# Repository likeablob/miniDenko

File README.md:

# miniDenko - A portable messaging device
`miniDenko` (Denko = 電光 is from "an electric scoreboard" in Japanese) is a portable messaging device.

Or LED Matrix + ESP8266 + MPU6050 + Modern Web framework(Vue.js + Buefy) = A hackable LED messaging platform

## Features
- Edit & save your message and show it up instantly.(Sub-second booting)
  - Also supports Japanese characters thanks to [Arduino-misakiUTF16](https://github.com/Tamakichi/Arduino-misakiUTF16) lib written by [[Tamakichi]](https://github.com/Tamakichi) san.
- Easily connectable with Phones, Laptops, etc. via WiFi.
  - Supports `STA`, `AP`, `AP_STA` modes to collaborate with the devices.
- Made from easily-obtainable parts. (See [#BOM](#BOM))
- Its [portable and slim shape](./openscad/minidenko-case-body-opaque.stl) fits in your (large) pocket.

- And as a latest gadget should be, equipped with the **Type-C** charging port.

## Project structure
- [`pio/`](./pio) - code for the firmware(PlatformIO)
- [`pio/webui/`](./pio/webui) - code for the WebUI(Vue.js + Buefy)
- [`kicad/`](./kicad) - PCB design (KiCad)
- [`gerber/`](./gerber) - PCB gerber files (KiCad)
- [`openscad/`](./openscad) - models for the 3D-printable case. (OpenSCAD)

## Gallery
|                                                                                                                                                                   | Descriptions              |
| ----------------------------------------------------------------------------------------------------------------------------------------------------------------- | ------------------------- |
|                                                                                 | Front view                |
|                                                                             | Side view (Charging port) |
|                                                                               | Side view (Power SW)      |
|                                                                                   | PCB                       |
|   | Web UI                    |

## BOM
| Name                                    | Quantity | Descriptions |
| --------------------------------------- | :------: | ------------ |
| ESP-12F (ESP8266 module)                |    1     |              |
| 32x8 LED matrix module (MAX7219)        |    1     |              |
| GY-521 (MPU6050 module)                 |    1     | 8 pins       |
| 350mAh LiPo battery                     |    1     | 19x36x8.5 mm |
| Type-C LiPo charging board (TP4056)     |    1     | 28x17.3 mm   |
| 10k ohm resistor (0805_2012Metric)      |    4     |              |
| 33k ohm resistor (0805_2012Metric)      |    1     |              |
| 1uF ceramic capacitor (0805_2012Metric) |    1     |              |
| 3.3V LDO xc6206p332mr (SOT-23)          |    1     |              |
| SPDT rocker switch (10x15 mm)           |    1     |              |
| M1.2 x 5 mm self tapping screw          |    4     |              |
| M2 x 6 mm self tapping screw            |    2     |              |

## Build instructions
https://hackaday.io/project/167747/instructions

## Refs
- https://www.thingiverse.com/thing:3876563
- https://hackaday.io/project/167747-minidenko
  
## License
MIT

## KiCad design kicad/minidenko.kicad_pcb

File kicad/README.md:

# miniDenko/PCB

## Prerequisites
- Install [KiCAD](https://platformio.org/) v5.0.1

## Credits
- [ESP-12E.kicad_mod](./lib_ext/ESP-12E.kicad_mod): borrowed from [jdunmire/kicad-ESP8266](https://github.com/jdunmire/kicad-ESP8266/tree/70e6530de5e3cae4ae77a4bca7d73b20a0af6baf)
- [MSK12C02.kicad_mod](./lib_ext/MSK12C02.kicad_mod): borrowed from [ElectronicCats/ElectronicCats-KiCad-Libraries](https://github.com/ElectronicCats/ElectronicCats-KiCad-Libraries/tree/df452181bf0b37c41caa9d8791b5432d5b44f4c0)

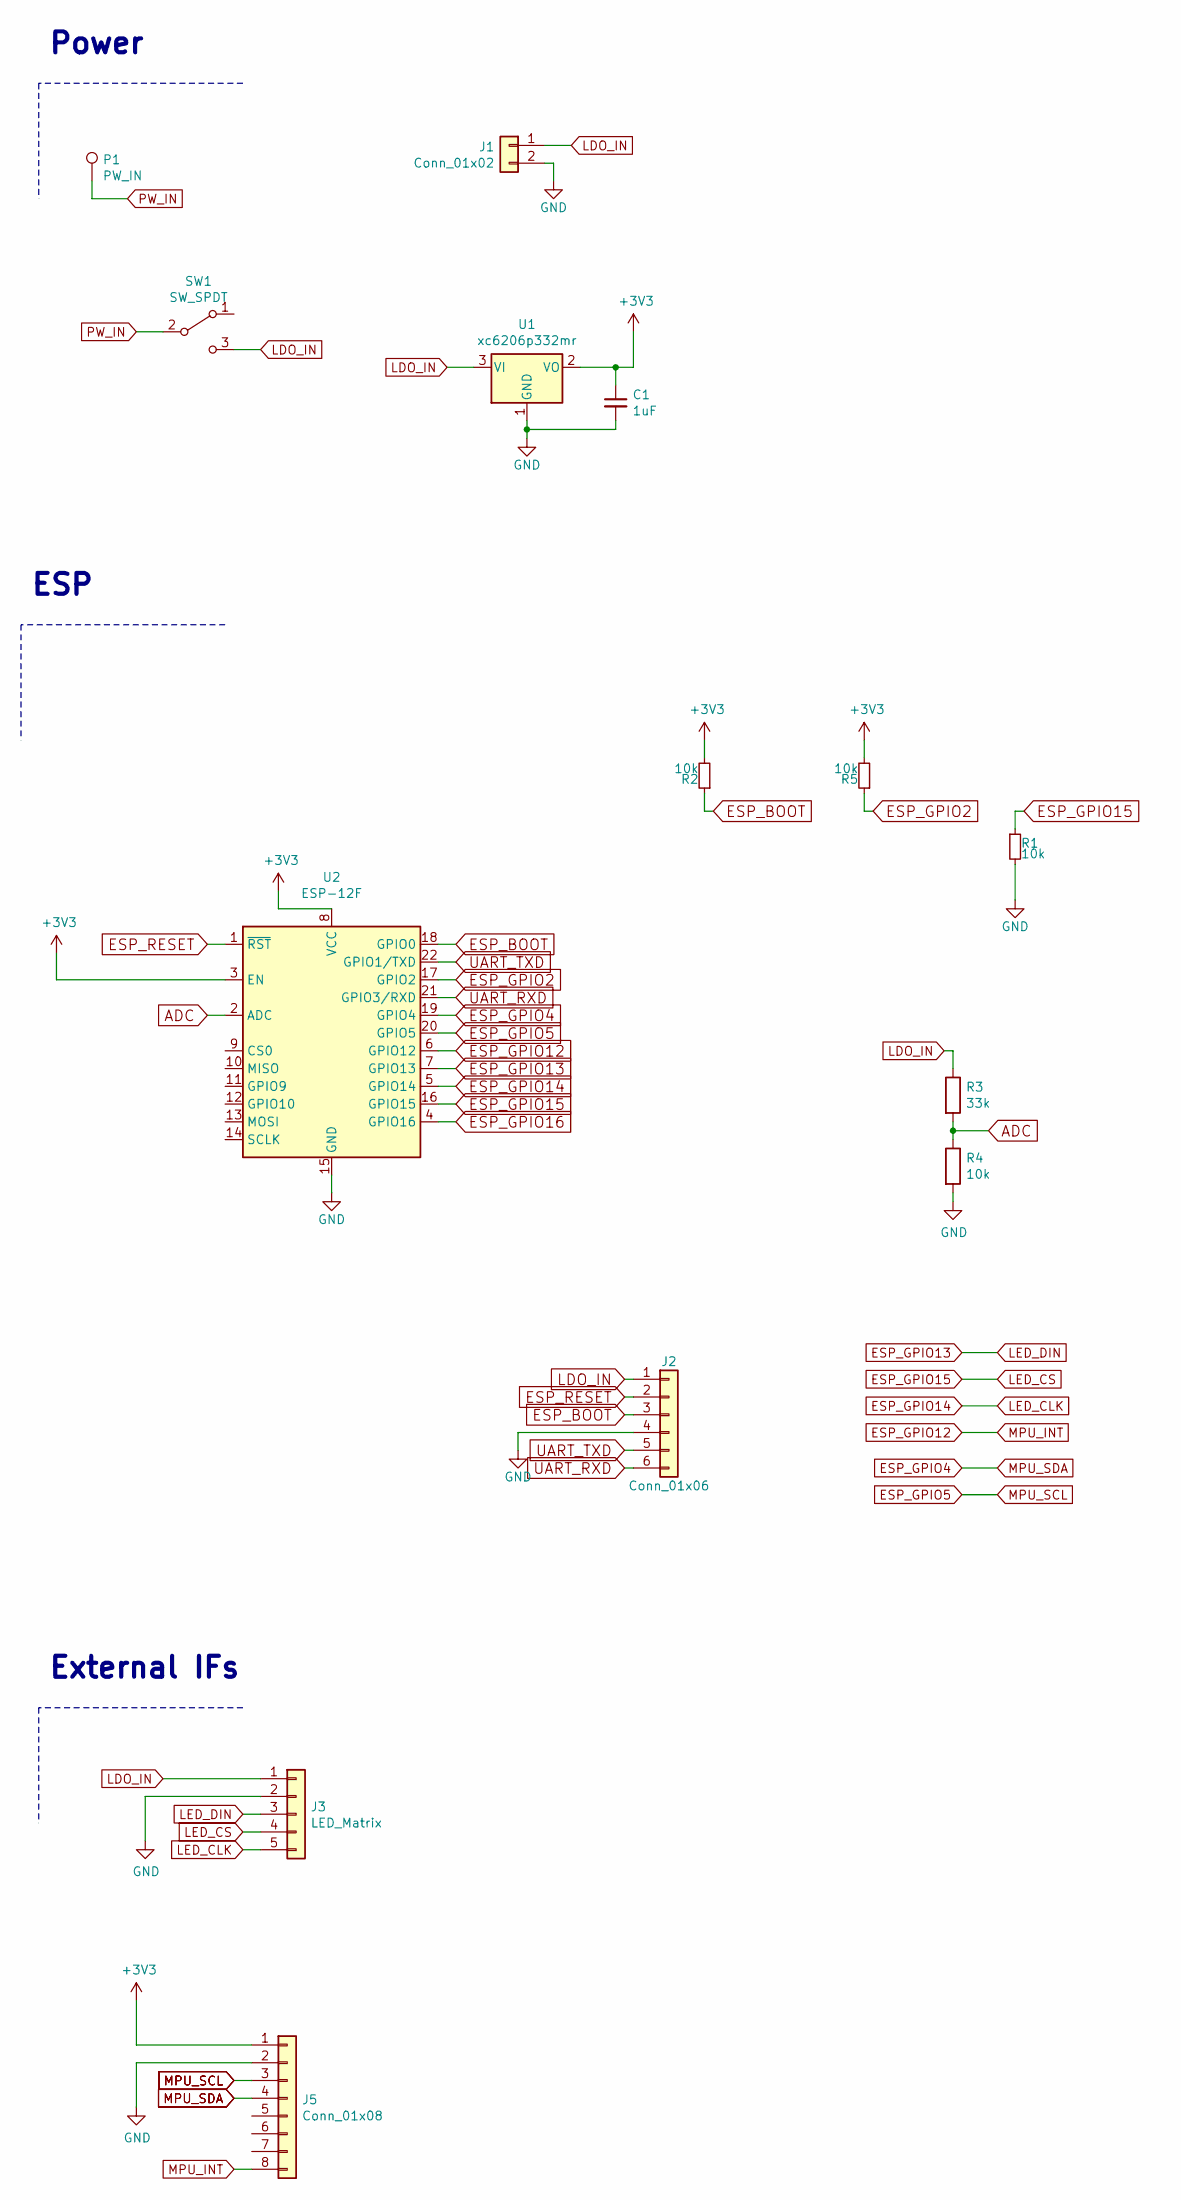
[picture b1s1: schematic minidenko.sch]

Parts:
C1: 1uF; C_0805_2012Metric_Pad1.15x1.40mm_HandSolder
J1: Conn_01x02; PinHeader_1x02_P2.54mm_Vertical
J2: Conn_01x06; PinHeader_1x06_P2.54mm_Vertical
J3: LED_Matrix; LED_Matrix_1x05_P2.54mm
J5: Conn_01x08; PinHeader_1x08_P2.54mm_Vertical
P1: PW_IN; TestPoint_Pad_1.5x1.5mm
R1, R2, R4, R5: 10k; R_0805_2012Metric
R3: 33k; R_0805_2012Metric
SW1: SW_SPDT; MSK12C02
U1: xc6206p332mr; SOT-23_Handsoldering
U2: ESP-12F; ESP-12E

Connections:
+3V3: C1.1, J5.1, R2.2, R5.2, U1.2 (VO), U2.3 (EN), U2.8 (VCC)
ADC: R3.2, R4.1, U2.2 (ADC)
ESP_BOOT: J2.3, R2.1, U2.18 (GPIO0)
ESP_GPIO2: R5.1, U2.17 (GPIO2)
ESP_GPIO4: J5.4, U2.19 (GPIO4)
ESP_GPIO5: J5.3, U2.20 (GPIO5)
ESP_GPIO12: J5.8, U2.6 (GPIO12)
ESP_GPIO13: J3.3, U2.7 (GPIO13)
ESP_GPIO14: J3.5, U2.5 (GPIO14)
ESP_GPIO15: J3.4, R1.1, U2.16 (GPIO15)
ESP_GPIO16: U2.4 (GPIO16)
ESP_RESET: J2.2, U2.1 (~RST)
GND: C1.2, J1.2, J2.4, J3.2, J5.2, R1.2, R4.2, U1.1 (GND), U2.15 (GND)
LDO_IN: J1.1, J2.1, J3.1, R3.1, SW1.3 (C), U1.3 (VI)
PW_IN: P1.1, SW1.2 (B)
UART_RXD: J2.6, U2.21 (GPIO3/RXD)
UART_TXD: J2.5, U2.22 (GPIO1/TXD)

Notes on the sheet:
ESP
Power
External IFs

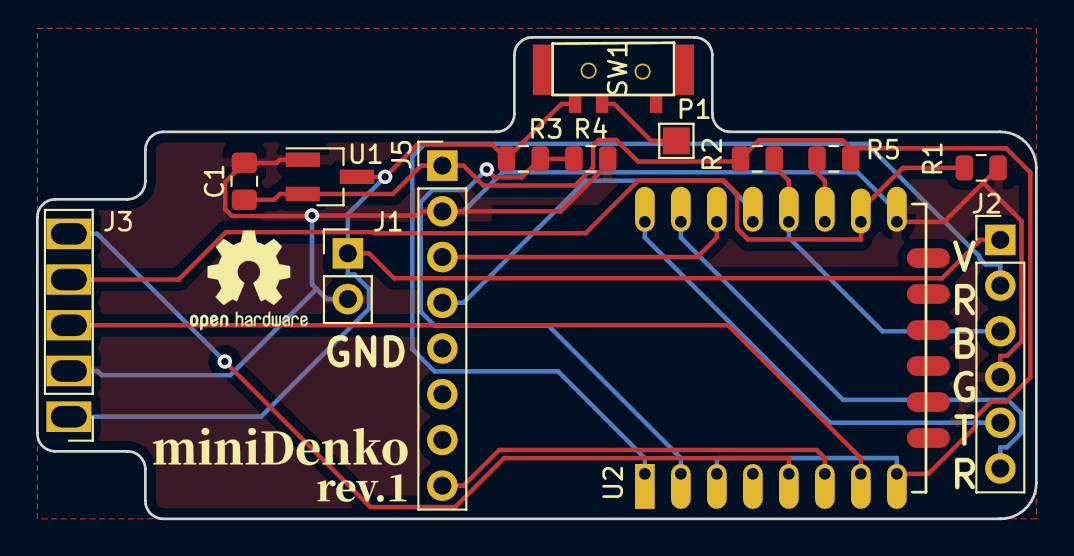
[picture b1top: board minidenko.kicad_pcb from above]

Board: 2 copper layers, 55.5 x 26.8 mm, 17 parts (1 on the bottom side), 16 nets.

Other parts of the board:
G1: LOGO; logo-minidenko-rev1
G2: OSHW-Logo2_7.3x6mm_SilkScreen
G3: LOGO; gomi_8x8

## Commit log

2019-09-24 Add files
2019-09-25 Add rev2 logo
2019-09-26 modify README.md format
2019-09-26 Add PCB files
2019-09-26 Upgrade dependencies
2019-09-26 Modify README.md - Add BOM - Minor tweak
2019-09-26 Modify README.md - Add Gellery section - Minor tweaks
2019-09-26 Modify openscad/README - Add print settings
2019-09-27 Fix validation for a void message
2019-09-29 Modify READMEs - Minor tweaks - Add pindef for the ISP port
2019-09-29 Add json-server/db.json
2020-06-07 Bump websocket-extensions from 0.1.3 to 0.1.4 in /pio/webui
    Bumps [websocket-extensions](https://github.com/faye/websocket-extensions-node) from 0.1.3 to 0.1.4.
    - [Release notes](https://github.com/faye/websocket-extensions-node/releases)
    - [Changelog](https://github.com/faye/websocket-extensions-node/blob/master/CHANGELOG.md)
    - [Commits](https://github.com/faye/websocket-extensions-node/compare/0.1.3...0.1.4)
2020-07-18 Bump lodash from 4.17.15 to 4.17.19 in /pio/webui
    Bumps [lodash](https://github.com/lodash/lodash) from 4.17.15 to 4.17.19.
    - [Release notes](https://github.com/lodash/lodash/releases)
    - [Commits](https://github.com/lodash/lodash/compare/4.17.15...4.17.19)
2020-07-31 Bump elliptic from 6.5.1 to 6.5.3 in /pio/webui
    Bumps [elliptic](https://github.com/indutny/elliptic) from 6.5.1 to 6.5.3.
    - [Release notes](https://github.com/indutny/elliptic/releases)
    - [Commits](https://github.com/indutny/elliptic/compare/v6.5.1...v6.5.3)
2020-09-04 Bump node-sass from 4.12.0 to 4.13.1 in /pio/webui
    Bumps [node-sass](https://github.com/sass/node-sass) from 4.12.0 to 4.13.1.
    - [Release notes](https://github.com/sass/node-sass/releases)
    - [Changelog](https://github.com/sass/node-sass/blob/master/CHANGELOG.md)
    - [Commits](https://github.com/sass/node-sass/compare/v4.12.0...v4.13.1)
2020-09-10 Bump http-proxy from 1.18.0 to 1.18.1 in /pio/webui
    Bumps [http-proxy](https://github.com/http-party/node-http-proxy) from 1.18.0 to 1.18.1.
    - [Release notes](https://github.com/http-party/node-http-proxy/releases)
    - [Changelog](https://github.com/http-party/node-http-proxy/blob/master/CHANGELOG.md)
    - [Commits](https://github.com/http-party/node-http-proxy/compare/1.18.0...1.18.1)
2020-11-25 Bump highlight.js from 9.15.10 to 9.18.5 in /pio/webui
    Bumps [highlight.js](https://github.com/highlightjs/highlight.js) from 9.15.10 to 9.18.5.
    - [Release notes](https://github.com/highlightjs/highlight.js/releases)
    - [Changelog](https://github.com/highlightjs/highlight.js/blob/9.18.5/CHANGES.md)
    - [Commits](https://github.com/highlightjs/highlight.js/compare/9.15.10...9.18.5)
2020-12-11 Bump ini from 1.3.5 to 1.3.8 in /pio/webui
    Bumps [ini](https://github.com/isaacs/ini) from 1.3.5 to 1.3.8.
    - [Release notes](https://github.com/isaacs/ini/releases)
    - [Commits](https://github.com/isaacs/ini/compare/v1.3.5...v1.3.8)
2021-01-05 Bump axios from 0.19.0 to 0.21.1 in /pio/webui
    Bumps [axios](https://github.com/axios/axios) from 0.19.0 to 0.21.1.
    - [Release notes](https://github.com/axios/axios/releases)
    - [Changelog](https://github.com/axios/axios/blob/v0.21.1/CHANGELOG.md)
    - [Commits](https://github.com/axios/axios/compare/v0.19.0...v0.21.1)
2021-03-09 Bump elliptic from 6.5.1 to 6.5.4 in /pio/webui
    Bumps [elliptic](https://github.com/indutny/elliptic) from 6.5.1 to 6.5.4.
    - [Release notes](https://github.com/indutny/elliptic/releases)
    - [Commits](https://github.com/indutny/elliptic/compare/v6.5.1...v6.5.4)
2021-03-31 Bump y18n from 3.2.1 to 3.2.2 in /pio/webui
    Bumps [y18n](https://github.com/yargs/y18n) from 3.2.1 to 3.2.2.
    - [Release notes](https://github.com/yargs/y18n/releases)
    - [Changelog](https://github.com/yargs/y18n/blob/master/CHANGELOG.md)
    - [Commits](https://github.com/yargs/y18n/commits)
2021-05-08 Bump url-parse from 1.4.7 to 1.5.1 in /pio/webui
    Bumps [url-parse](https://github.com/unshiftio/url-parse) from 1.4.7 to 1.5.1.
    - [Release notes](https://github.com/unshiftio/url-parse/releases)
    - [Commits](https://github.com/unshiftio/url-parse/compare/1.4.7...1.5.1)
2021-05-10 Bump lodash from 4.17.15 to 4.17.21 in /pio/webui
    Bumps [lodash](https://github.com/lodash/lodash) from 4.17.15 to 4.17.21.
    - [Release notes](https://github.com/lodash/lodash/releases)
    - [Commits](https://github.com/lodash/lodash/compare/4.17.15...4.17.21)
2021-05-11 Bump hosted-git-info from 2.8.4 to 2.8.9 in /pio/webui
    Bumps [hosted-git-info](https://github.com/npm/hosted-git-info) from 2.8.4 to 2.8.9.
    - [Release notes](https://github.com/npm/hosted-git-info/releases)
    - [Changelog](https://github.com/npm/hosted-git-info/blob/v2.8.9/CHANGELOG.md)
    - [Commits](https://github.com/npm/hosted-git-info/compare/v2.8.4...v2.8.9)
2021-05-25 Bump browserslist from 4.7.0 to 4.16.6 in /pio/webui
    Bumps [browserslist](https://github.com/browserslist/browserslist) from 4.7.0 to 4.16.6.
    - [Release notes](https://github.com/browserslist/browserslist/releases)
    - [Changelog](https://github.com/browserslist/browserslist/blob/main/CHANGELOG.md)
    - [Commits](https://github.com/browserslist/browserslist/compare/4.7.0...4.16.6)
2021-05-28 Bump dns-packet from 1.3.1 to 1.3.4 in /pio/webui
    Bumps [dns-packet](https://github.com/mafintosh/dns-packet) from 1.3.1 to 1.3.4.
    - [Release notes](https://github.com/mafintosh/dns-packet/releases)
    - [Changelog](https://github.com/mafintosh/dns-packet/blob/master/CHANGELOG.md)
    - [Commits](https://github.com/mafintosh/dns-packet/compare/v1.3.1...v1.3.4)
2021-06-05 Bump ws from 6.2.1 to 6.2.2 in /pio/webui
    Bumps [ws](https://github.com/websockets/ws) from 6.2.1 to 6.2.2.
    - [Release notes](https://github.com/websockets/ws/releases)
    - [Commits](https://github.com/websockets/ws/commits)
    ---
    updated-dependencies:
    - dependency-name: ws
2021-08-11 Bump path-parse from 1.0.6 to 1.0.7 in /pio/webui
    Bumps [path-parse](https://github.com/jbgutierrez/path-parse) from 1.0.6 to 1.0.7.
    - [Release notes](https://github.com/jbgutierrez/path-parse/releases)
    - [Commits](https://github.com/jbgutierrez/path-parse/commits/v1.0.7)
    ---
    updated-dependencies:
    - dependency-name: path-parse
2021-10-06 Bump url-parse from 1.4.7 to 1.5.3 in /pio/webui
    Bumps [url-parse](https://github.com/unshiftio/url-parse) from 1.4.7 to 1.5.3.
    - [Release notes](https://github.com/unshiftio/url-parse/releases)
    - [Commits](https://github.com/unshiftio/url-parse/compare/1.4.7...1.5.3)
    ---
    updated-dependencies:
    - dependency-name: url-parse
2022-02-10 Bump node-sass from 4.12.0 to 7.0.0 in /pio/webui
    Bumps [node-sass](https://github.com/sass/node-sass) from 4.12.0 to 7.0.0.
    - [Release notes](https://github.com/sass/node-sass/releases)
    - [Changelog](https://github.com/sass/node-sass/blob/master/CHANGELOG.md)
    - [Commits](https://github.com/sass/node-sass/compare/v4.12.0...v7.0.0)
    ---
    updated-dependencies:
2022-02-18 Bump url-parse from 1.4.7 to 1.5.7 in /pio/webui
    Bumps [url-parse](https://github.com/unshiftio/url-parse) from 1.4.7 to 1.5.7.
    - [Release notes](https://github.com/unshiftio/url-parse/releases)
    - [Commits](https://github.com/unshiftio/url-parse/compare/1.4.7...1.5.7)
    ---
    updated-dependencies:
    - dependency-name: url-parse
2022-02-26 Bump url-parse from 1.4.7 to 1.5.10 in /pio/webui
    Bumps [url-parse](https://github.com/unshiftio/url-parse) from 1.4.7 to 1.5.10.
    - [Release notes](https://github.com/unshiftio/url-parse/releases)
    - [Commits](https://github.com/unshiftio/url-parse/compare/1.4.7...1.5.10)
    ---
    updated-dependencies:
    - dependency-name: url-parse
2022-06-01 Bump eventsource from 1.0.7 to 1.1.1 in /pio/webui
    Bumps [eventsource](https://github.com/EventSource/eventsource) from 1.0.7 to 1.1.1.
    - [Release notes](https://github.com/EventSource/eventsource/releases)
    - [Changelog](https://github.com/EventSource/eventsource/blob/master/HISTORY.md)
    - [Commits](https://github.com/EventSource/eventsource/compare/v1.0.7...v1.1.1)
    ---
    updated-dependencies:
2022-06-22 Bump shell-quote from 1.7.2 to 1.7.3 in /pio/webui
    Bumps [shell-quote](https://github.com/substack/node-shell-quote) from 1.7.2 to 1.7.3.
    - [Release notes](https://github.com/substack/node-shell-quote/releases)
    - [Changelog](https://github.com/substack/node-shell-quote/blob/master/CHANGELOG.md)
    - [Commits](https://github.com/substack/node-shell-quote/compare/v1.7.2...1.7.3)
    ---
    updated-dependencies:
2022-07-20 Bump terser from 4.3.2 to 4.8.1 in /pio/webui
    Bumps [terser](https://github.com/terser/terser) from 4.3.2 to 4.8.1.
    - [Release notes](https://github.com/terser/terser/releases)
    - [Changelog](https://github.com/terser/terser/blob/master/CHANGELOG.md)
    - [Commits](https://github.com/terser/terser/commits)
    ---
    updated-dependencies:
2022-12-04 Bump decode-uri-component from 0.2.0 to 0.2.2 in /pio/webui
    Bumps [decode-uri-component](https://github.com/SamVerschueren/decode-uri-component) from 0.2.0 to 0.2.2.
    - [Release notes](https://github.com/SamVerschueren/decode-uri-component/releases)
    - [Commits](https://github.com/SamVerschueren/decode-uri-component/compare/v0.2.0...v0.2.2)
    ---
    updated-dependencies:
    - dependency-name: decode-uri-component
2022-12-10 Bump qs from 6.5.2 to 6.5.3 in /pio/webui
    Bumps [qs](https://github.com/ljharb/qs) from 6.5.2 to 6.5.3.
    - [Release notes](https://github.com/ljharb/qs/releases)
    - [Changelog](https://github.com/ljharb/qs/blob/main/CHANGELOG.md)
    - [Commits](https://github.com/ljharb/qs/compare/v6.5.2...v6.5.3)
    ---
    updated-dependencies:
2022-12-11 Bump express from 4.17.1 to 4.18.2 in /pio/webui
    Bumps [express](https://github.com/expressjs/express) from 4.17.1 to 4.18.2.
    - [Release notes](https://github.com/expressjs/express/releases)
    - [Changelog](https://github.com/expressjs/express/blob/master/History.md)
    - [Commits](https://github.com/expressjs/express/compare/4.17.1...4.18.2)
    ---
    updated-dependencies:
